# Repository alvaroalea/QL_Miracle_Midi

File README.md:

# Miracle MIDI Interface for QL
A reverse engineering exercice using the Sinclair QL Midi Interface as target

Licensed under Cern OHL-S - https://ohwr.org/cern_ohl_s_v2.txt

## WARNING: DO NOT USE THIS PROJECT IS NOT TESTED AND MISSING THINGS

This is not a functional item, it's only a exercice to reinforce my skills in Kicad EDA Software.

This project match schematic found on internet of the interface.

## Information
There is very few information about this interface.
Only 1 picture has been found on internet, and none of the internals of the interface.

There is information indicating that the interface is buggy and do not work well.

There is also information about a software and hardware patch to be able to work with super gold card.

There is only one software (with source code) available for this interface.

## Comparative

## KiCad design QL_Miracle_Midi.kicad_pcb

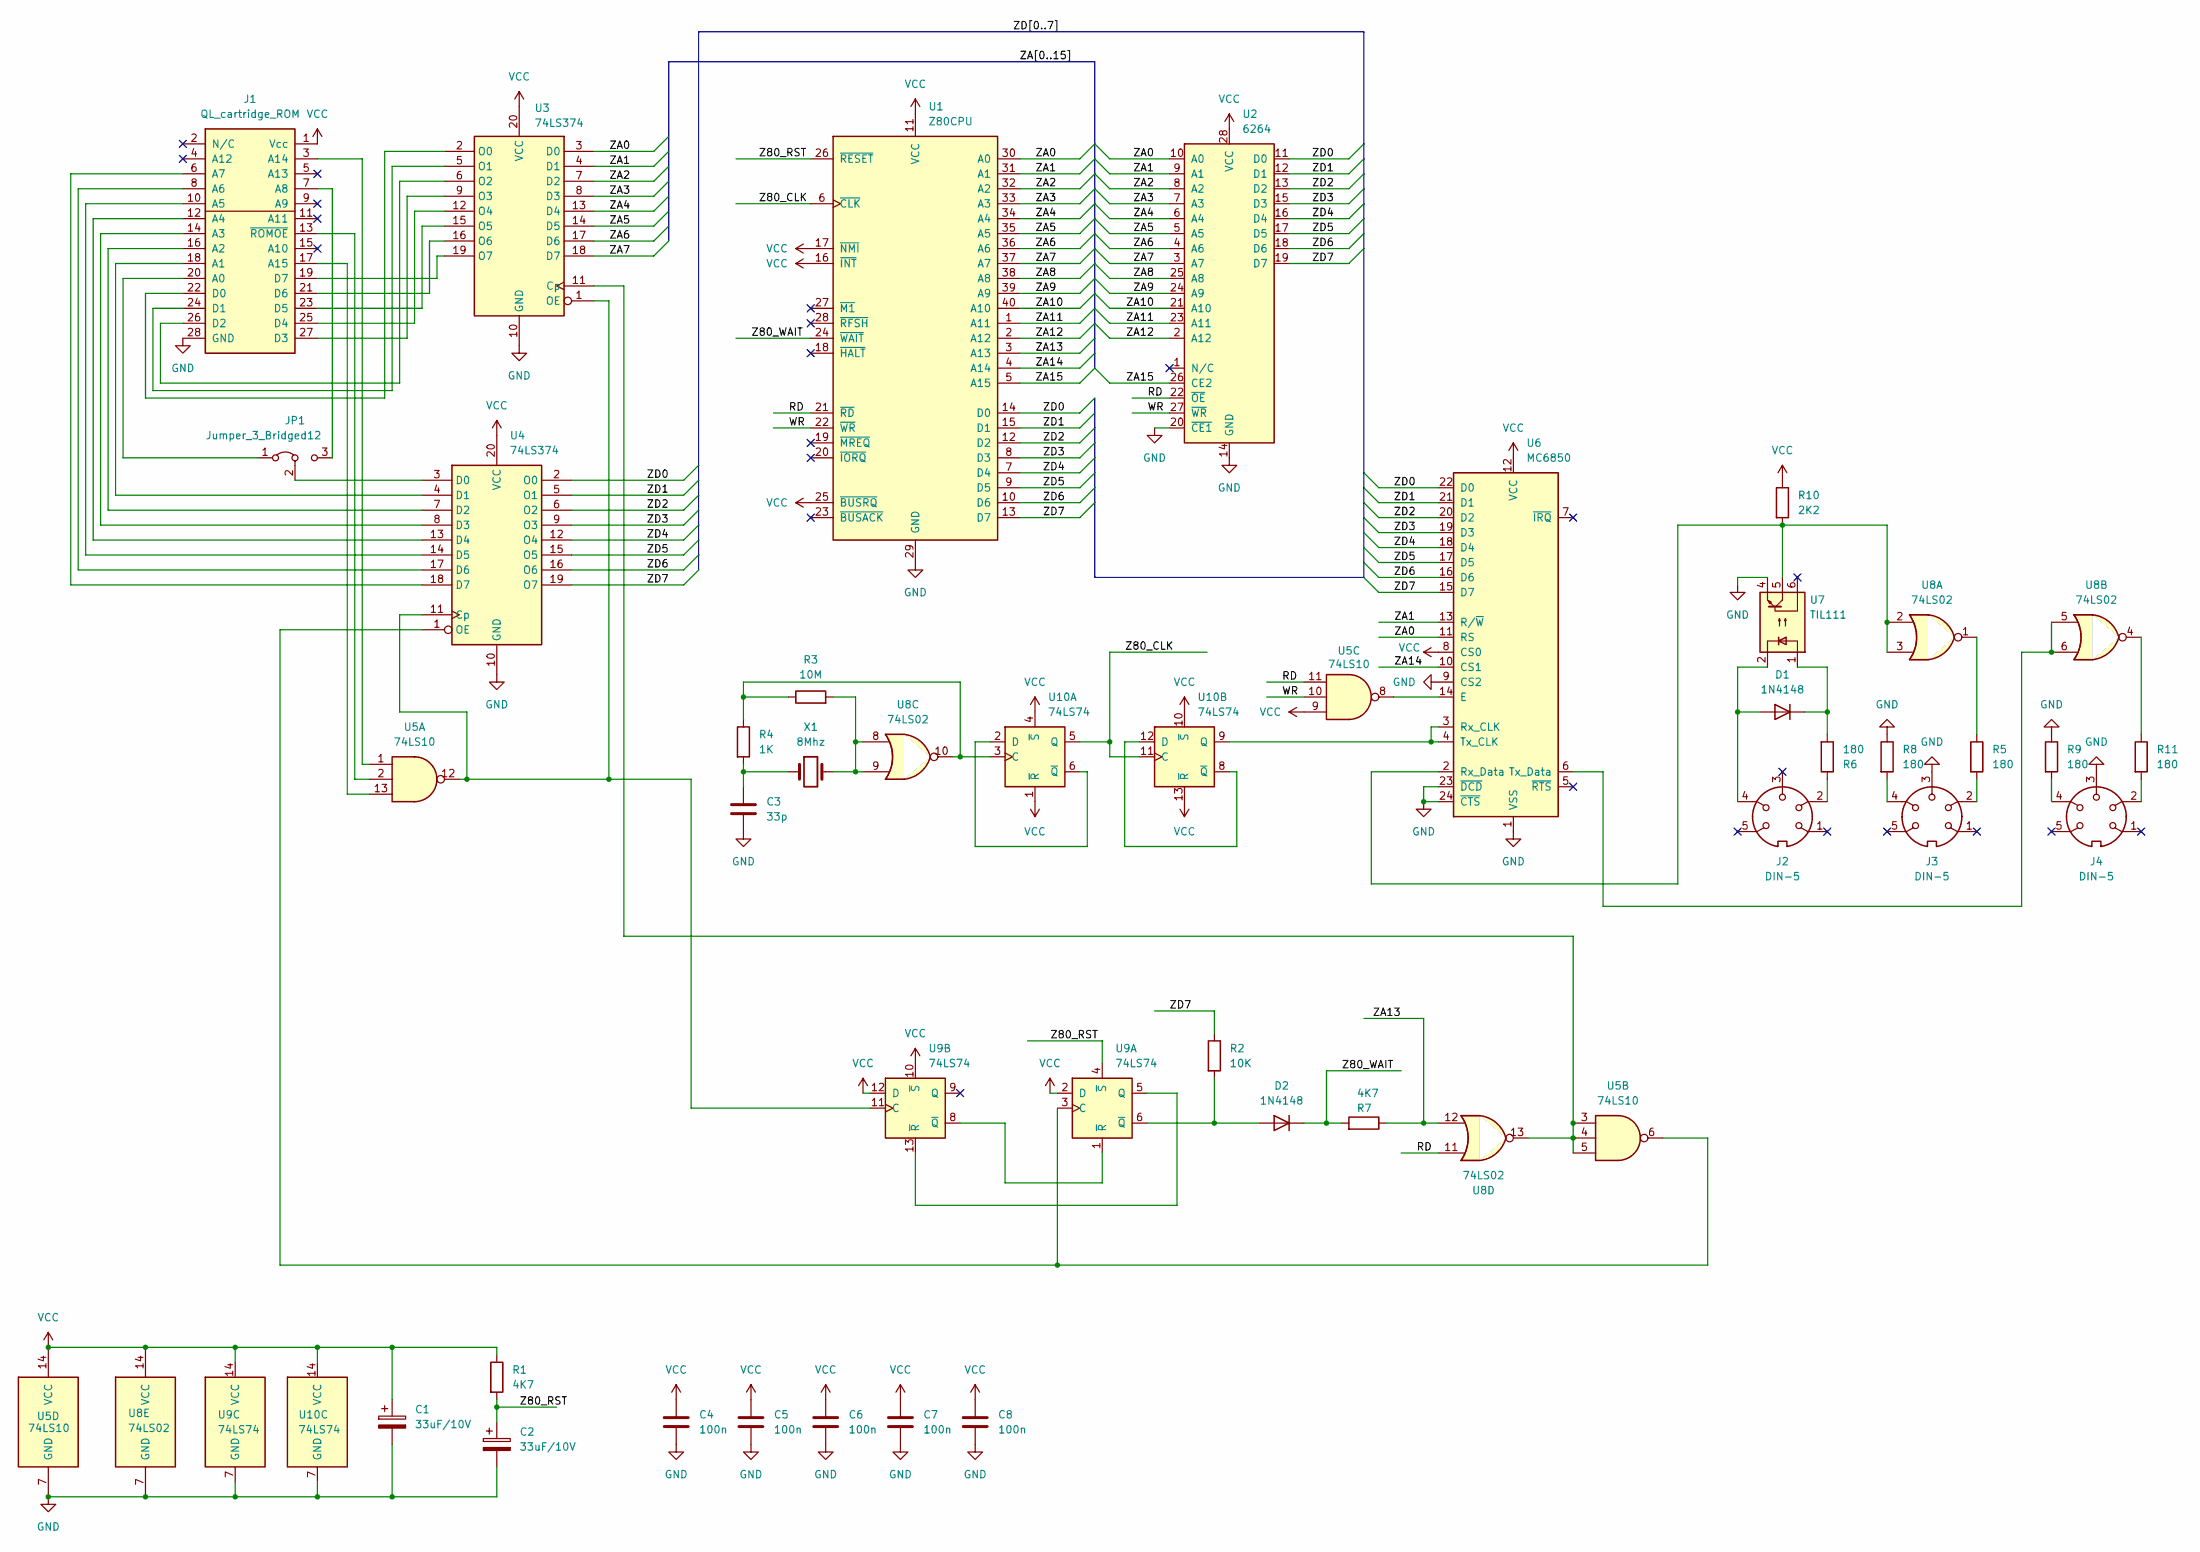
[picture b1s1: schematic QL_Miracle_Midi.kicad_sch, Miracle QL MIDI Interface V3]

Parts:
C1, C2: 33uF/10V; CP_Axial_L11.0mm_D5.0mm_P18.00mm_Horizontal
C3: 33p; C_Disc_D3.8mm_W2.6mm_P2.50mm
C4, C5, C6, C7, C8: 100n; C_Disc_D4.3mm_W1.9mm_P5.00mm
D1, D2: 1N4148; D_DO-35_SOD27_P2.54mm_Vertical_KathodeUp
J1: QL_cartridge_ROM; CART_QL_EDGE
J2, J3, J4: DIN-5; DIN-5-female-pcb-horizontal-miracle
JP1: Jumper_3_Bridged12; SolderJumper-3_P1.3mm_Open_Pad1.0x1.5mm
R1: 4K7; R_Axial_DIN0207_L6.3mm_D2.5mm_P10.16mm_Horizontal
R2: 10K; R_Axial_DIN0207_L6.3mm_D2.5mm_P2.54mm_Vertical
R3: 10M; R_Axial_DIN0207_L6.3mm_D2.5mm_P2.54mm_Vertical
R4: 1K; R_Axial_DIN0207_L6.3mm_D2.5mm_P2.54mm_Vertical
R5, R6, R8, R9, R11: 180; R_Axial_DIN0207_L6.3mm_D2.5mm_P2.54mm_Vertical
R7: 4K7; R_Axial_DIN0207_L6.3mm_D2.5mm_P2.54mm_Vertical
R10: 2K2; R_Axial_DIN0207_L6.3mm_D2.5mm_P2.54mm_Vertical
U1: Z80CPU; DIP-40_W15.24mm_Socket
U2: 6264; DIP-28_W15.24mm_Socket
U3, U4: 74LS374; DIP-20_W7.62mm_Socket
U5: 74LS10; DIP-14_W7.62mm_Socket
U6: MC6850; DIP-24_W15.24mm_Socket
U7: TIL111; DIP-6_W7.62mm_Socket
U8: 74LS02; DIP-14_W7.62mm_Socket
U9, U10: 74LS74; DIP-14_W7.62mm_Socket
X1: 8Mhz; Crystal_HC49-U_Vertical

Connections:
/RD: U1.21 (~RD), U2.22 (~OE), U5.11, U8.11
/WR: U1.22 (~WR), U2.27 (~WR), U5.10
/Z80_CLK: U1.6 (~CLK), U10.5 (Q), U10.11 (C)
/Z80_RST: C2.1, R1.2, U1.26 (~RESET), U9.4 (~S)
/Z80_WAIT: D2.1 (K), R7.2, U1.24 (~WAIT)
/ZA0: U1.30 (A0), U2.10 (A0), U3.3 (D0), U6.11 (RS)
/ZA1: U1.31 (A1), U2.9 (A1), U3.4 (D1), U6.13 (R/~W)
/ZA2: U1.32 (A2), U2.8 (A2), U3.7 (D2)
/ZA3: U1.33 (A3), U2.7 (A3), U3.8 (D3)
/ZA4: U1.34 (A4), U2.6 (A4), U3.13 (D4)
/ZA5: U1.35 (A5), U2.5 (A5), U3.14 (D5)
/ZA6: U1.36 (A6), U2.4 (A6), U3.17 (D6)
/ZA7: U1.37 (A7), U2.3 (A7), U3.18 (D7)
/ZA8: U1.38 (A8), U2.25 (A8)
/ZA9: U1.39 (A9), U2.24 (A9)
/ZA10: U1.40 (A10), U2.21 (A10)
/ZA11: U1.1 (A11), U2.23 (A11)
/ZA12: U1.2 (A12), U2.2 (A12)
/ZA13: R7.1, U1.3 (A13), U8.12
/ZA14: U1.4 (A14), U6.10 (CS1)
/ZA15: U1.5 (A15), U2.26 (CE2)
/ZD0: U1.14 (D0), U2.11 (D0), U4.2 (O0), U6.22 (D0)
/ZD1: U1.15 (D1), U2.12 (D1), U4.5 (O1), U6.21 (D1)
/ZD2: U1.12 (D2), U2.13 (D2), U4.6 (O2), U6.20 (D2)
/ZD3: U1.8 (D3), U2.15 (D3), U4.9 (O3), U6.19 (D3)
/ZD4: U1.7 (D4), U2.16 (D4), U4.12 (O4), U6.18 (D4)
/ZD5: U1.9 (D5), U2.17 (D5), U4.15 (O5), U6.17 (D5)
/ZD6: U1.10 (D6), U2.18 (D6), U4.16 (O6), U6.16 (D6)
/ZD7: R2.1, U1.13 (D7), U2.19 (D7), U4.19 (O7), U6.15 (D7)
GND: C1.2, C2.2, C3.2, C4.2, C5.2, C6.2, C7.2, C8.2, J1.28 (GND), J3.3, J4.3, R8.1, R9.1, U1.29 (GND), U2.14 (GND), U2.20 (~CE1), U3.10 (GND), U4.10 (GND), U5.7 (GND), U6.1 (VSS), U6.9 (CS2), U6.23 (~DCD), U6.24 (~CTS), U7.4, U8.7 (GND), U9.7 (GND), U10.7 (GND)
unnamed: C3.1, R4.2, X1.1
unnamed: D1.2 (A), J2.4, U7.2
unnamed: D1.1 (K), R6.2, U7.1
unnamed: D2.2 (A), R2.2, U9.6 (~Q)
unnamed: J1.20 (A0), JP1.1 (A)
unnamed: J1.18 (A1), U4.4 (D1)
unnamed: J1.16 (A2), U4.7 (D2)
unnamed: J1.14 (A3), U4.8 (D3)
unnamed: J1.12 (A4), U4.13 (D4)
unnamed: J1.10 (A5), U4.14 (D5)
unnamed: J1.8 (A6), U4.17 (D6)
unnamed: J1.6 (A7), U4.18 (D7)
unnamed: J1.7 (A8), JP1.3 (B)
unnamed: J1.3 (A14), U5.1
unnamed: J1.17 (A15), U5.13
unnamed: J1.22 (D0), U3.2 (O0)
unnamed: J1.24 (D1), U3.5 (O1)
unnamed: J1.26 (D2), U3.6 (O2)
unnamed: J1.27 (D3), U3.9 (O3)
unnamed: J1.25 (D4), U3.12 (O4)
unnamed: J1.23 (D5), U3.15 (O5)
unnamed: J1.21 (D6), U3.16 (O6)
unnamed: J1.19 (D7), U3.19 (O7)
unnamed: J1.13 (~ROMOE), U5.2
unnamed: J2.2, R6.1
unnamed: J3.2, R5.2
unnamed: J3.4, R8.2
unnamed: J4.2, R11.2
unnamed: J4.4, R9.2
unnamed: JP1.2 (C), U4.3 (D0)
unnamed: R3.2, U8.8, U8.9, X1.2
unnamed: R5.1, U8.1
unnamed: R11.1, U8.4
unnamed: U3.11 (Cp), U5.3, U5.4, U5.5, U8.13
unnamed: U3.1 (OE), U4.11 (Cp), U5.12, U9.11 (C)
unnamed: U4.1 (OE), U5.6, U9.3 (C)
unnamed: U5.8, U6.14 (E)
unnamed: R10.2, U6.2 (Rx_Data), U7.5, U8.2, U8.3
unnamed: U6.6 (Tx_Data), U8.5, U8.6
unnamed: U9.5 (Q), U9.13 (~R)
unnamed: U9.1 (~R), U9.8 (~Q)
unnamed: R3.1, R4.1, U8.10, U10.3 (C)
unnamed: U10.2 (D), U10.6 (~Q)
unnamed: U10.8 (~Q), U10.12 (D)
unnamed: U6.3 (Rx_CLK), U6.4 (Tx_CLK), U10.9 (Q)
VCC: C1.1, C4.1, C5.1, C6.1, C7.1, C8.1, J1.1 (Vcc), R1.1, R10.1, U1.11 (VCC), U1.16 (~INT), U1.17 (~NMI), U1.25 (~BUSRQ), U2.28 (VCC), U3.20 (VCC), U4.20 (VCC), U5.9, U5.14 (VCC), U6.8 (CS0), U6.12 (VCC), U8.14 (VCC), U9.2 (D), U9.10 (~S), U9.12 (D), U9.14 (VCC), U10.1 (~R), U10.4 (~S), U10.10 (~S), U10.13 (~R), U10.14 (VCC)

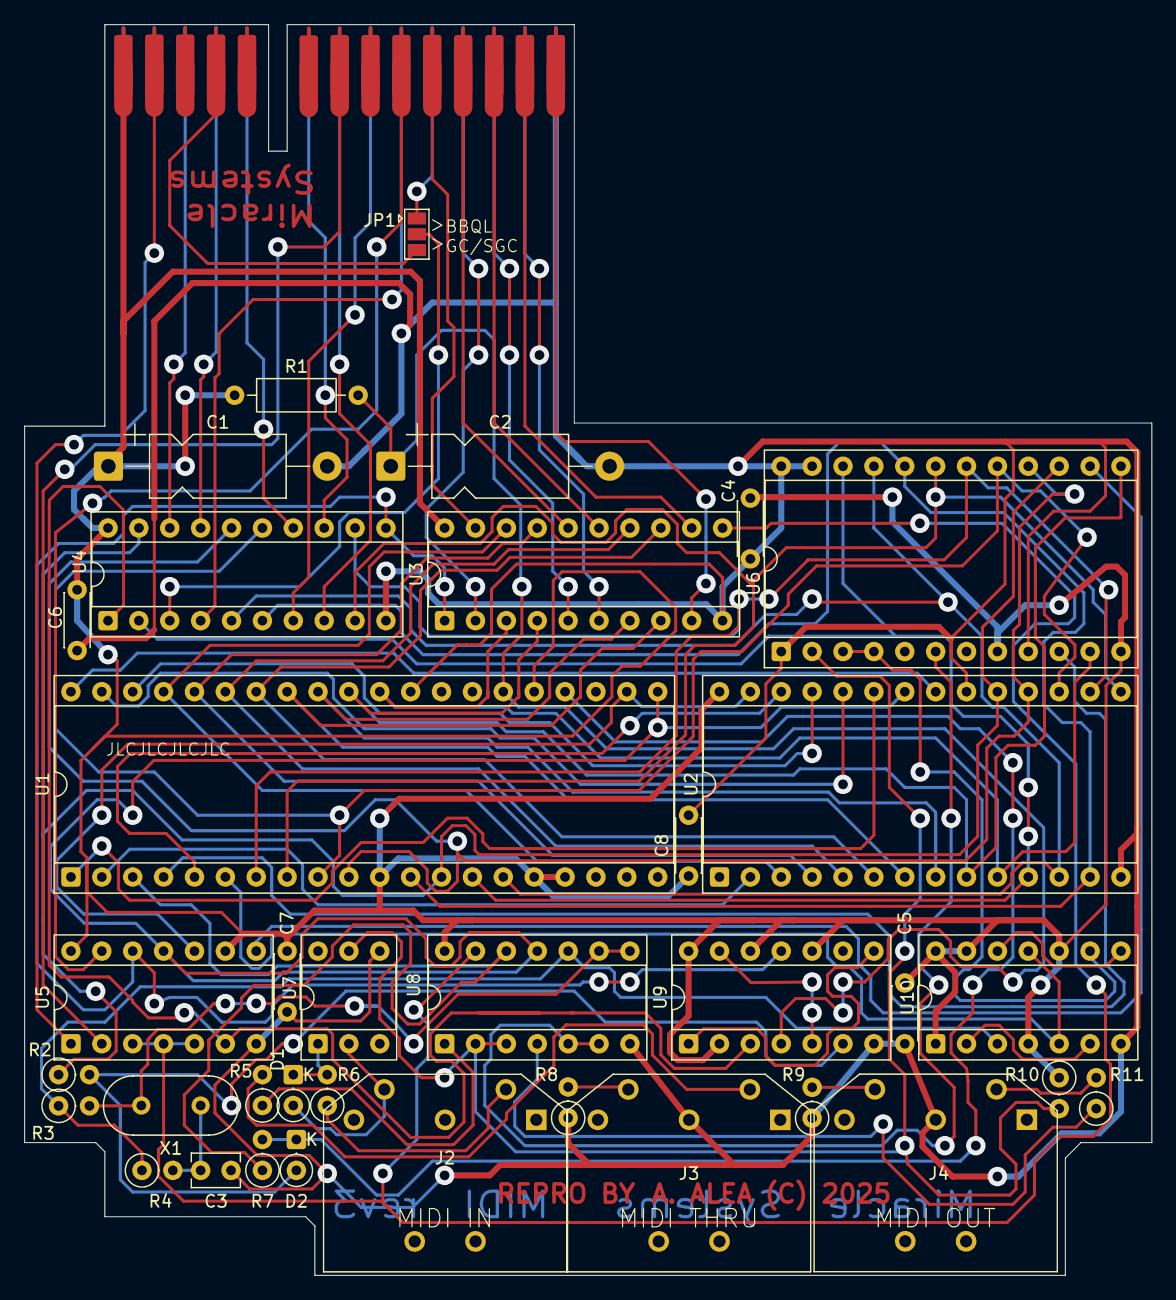
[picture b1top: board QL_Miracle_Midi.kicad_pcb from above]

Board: 2 copper layers, 92.7 x 102.9 mm, 37 parts (0 on the bottom side), 76 nets.

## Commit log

2025-07-27 initial
2025-12-04 pinout of midi update
2025-12-04 now based on real PCB
2025-12-09 a track
2026-02-20 finish route

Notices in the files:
QL_Miracle_Midi.kicad_pcb:
(C) 2025
